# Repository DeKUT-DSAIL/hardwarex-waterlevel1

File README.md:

## hardwarex-waterlevel1
### A Low Cost LoRa Based River Water Level Data Acquisition System (Design Files)
#### Contents
- Arduino Nano based stage monitoring system - Kicad design files (etching pdf available)
- Multitech mDot based stage monitoring system - Kicad design files (etching pdf available)
- Arduino Nano based stage monitoring system - Arduino IDE code (Firmware)
- TTN (The Things Network) payload formatter for the Multitech mDot based stage monitoring system (in JavaScript)

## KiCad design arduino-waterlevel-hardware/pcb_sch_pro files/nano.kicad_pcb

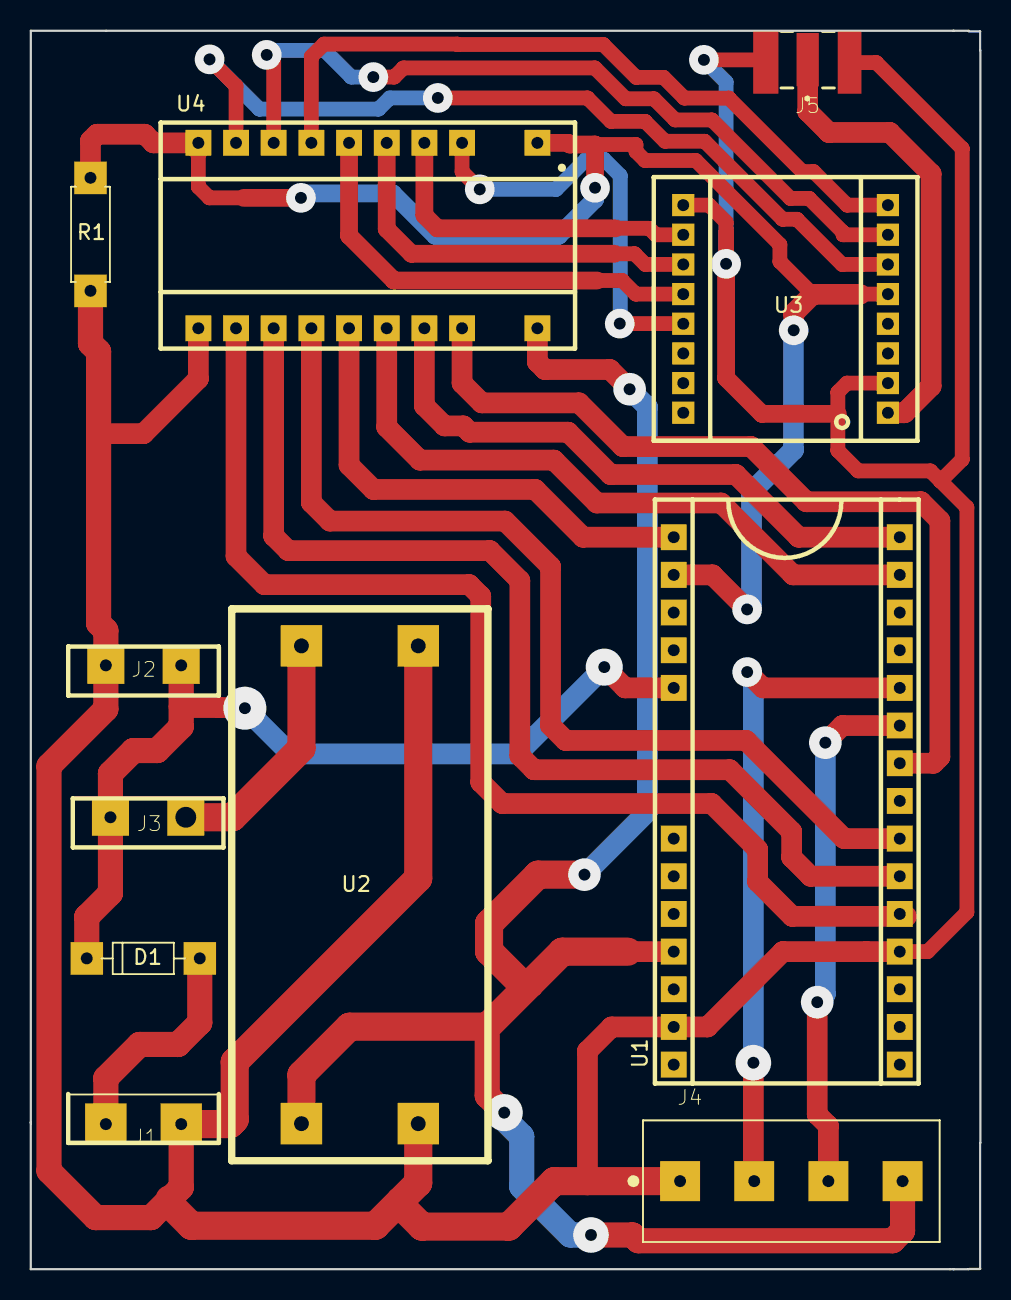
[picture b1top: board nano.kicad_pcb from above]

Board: 2 copper layers, 64.0 x 83.5 mm, 11 parts (0 on the bottom side), 23 nets.

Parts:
D1: D_DO-35_SOD27_P7.62mm_Horizontal
J1, J2, J3: TE_282815-2
J4: TE_282836-4
J5: SAMTEC_SMA-J-P-H-ST-EM1
R1: R_Axial_DIN0207_L6.3mm_D2.5mm_P7.62mm_Horizontal
U1: nano
U2: MT3608
U3: brake1
U4: SHIFT

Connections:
GND: J1.1, J2.1, J4.1, J5.2_1, J5.2_2, J5.3_1, J5.3_2, R1.1, U1.14, U1.19, U2.2, U2.4, U3.2, U3.9, U4.11
unnamed: D1.1, J2.2, J3.1
unnamed: D1.2, J1.2
unnamed: J3.2, U2.1
unnamed: J4.2, U1.26
unnamed: J4.3, U1.25
unnamed: J4.4, U1.12, U2.3, U4.20
unnamed: J5.1, U3.1
unnamed: R1.2, U1.2, U3.5, U4.1, U4.10
unnamed: U1.1, U4.15
unnamed: U1.20, U4.12
unnamed: U1.21, U4.13
unnamed: U1.22, U4.14
unnamed: U1.24, U4.18
unnamed: U1.29, U4.16
unnamed: U1.30, U4.17
unnamed: U3.6, U4.9
unnamed: U3.7, U4.8
unnamed: U3.8, U4.7
unnamed: U3.10, U4.4
unnamed: U3.11, U4.5
unnamed: U3.12, U4.6
unnamed: U3.13, U4.3

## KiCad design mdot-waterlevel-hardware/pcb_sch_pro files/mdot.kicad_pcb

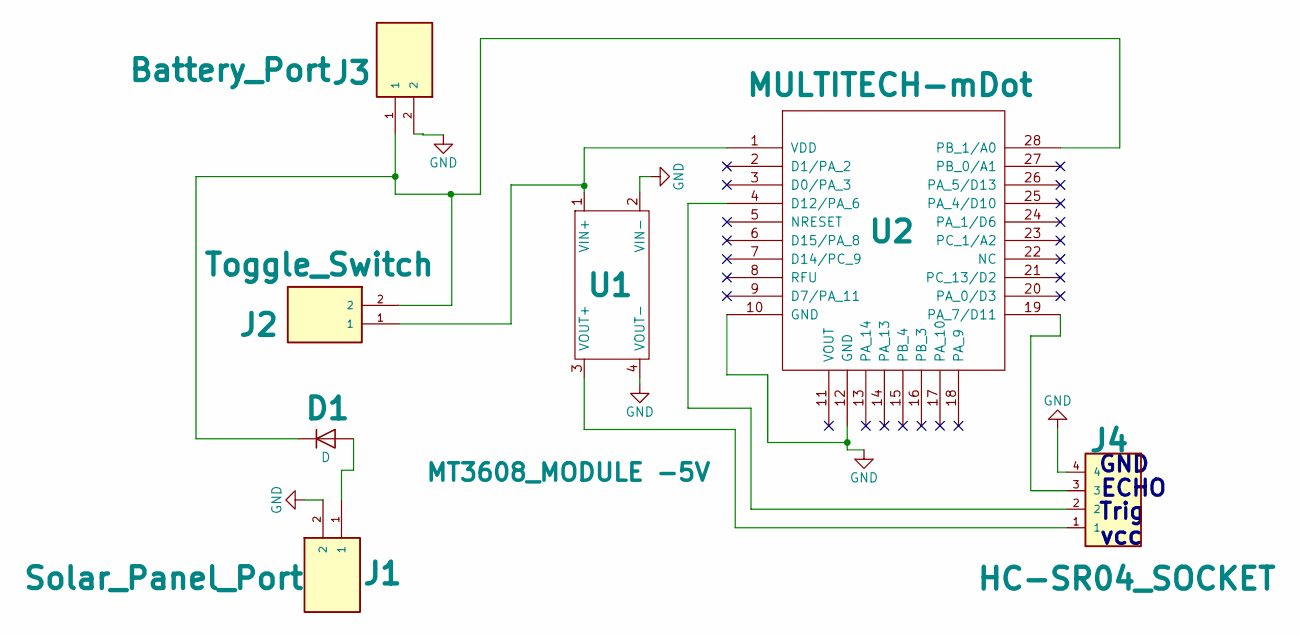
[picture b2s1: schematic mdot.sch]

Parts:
D1: D; D_5W_P12.70mm_Horizontal
J1: Solar_Panel_Port; TE_282815-2
J2: Toggle_Switch; TE_282815-2
J3: Battery_Port; TE_282815-2
J4: HC-SR04_SOCKET; TE_282836-4
U1: MT3608_MODULE -5V; MT3608
U2: MULTITECH-mDot; MDOT_TRIAL_BAT_CHARGER

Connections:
GND: J1.2, J3.2, J4.4, U1.2 (VIN-), U1.4 (VOUT-), U2.10 (GND), U2.12 (GND)
unnamed: D1.1 (K), J2.2, J3.1, U2.28 (PB_1/A0)
unnamed: D1.2 (A), J1.1
unnamed: J2.1, U1.1 (VIN+), U2.1 (VDD)
unnamed: J4.1, U1.3 (VOUT+)
unnamed: J4.2, U2.4 (D12/PA_6)
unnamed: J4.3, U2.19 (PA_7/D11)

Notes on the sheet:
vcc
Trig
ECHO
GND

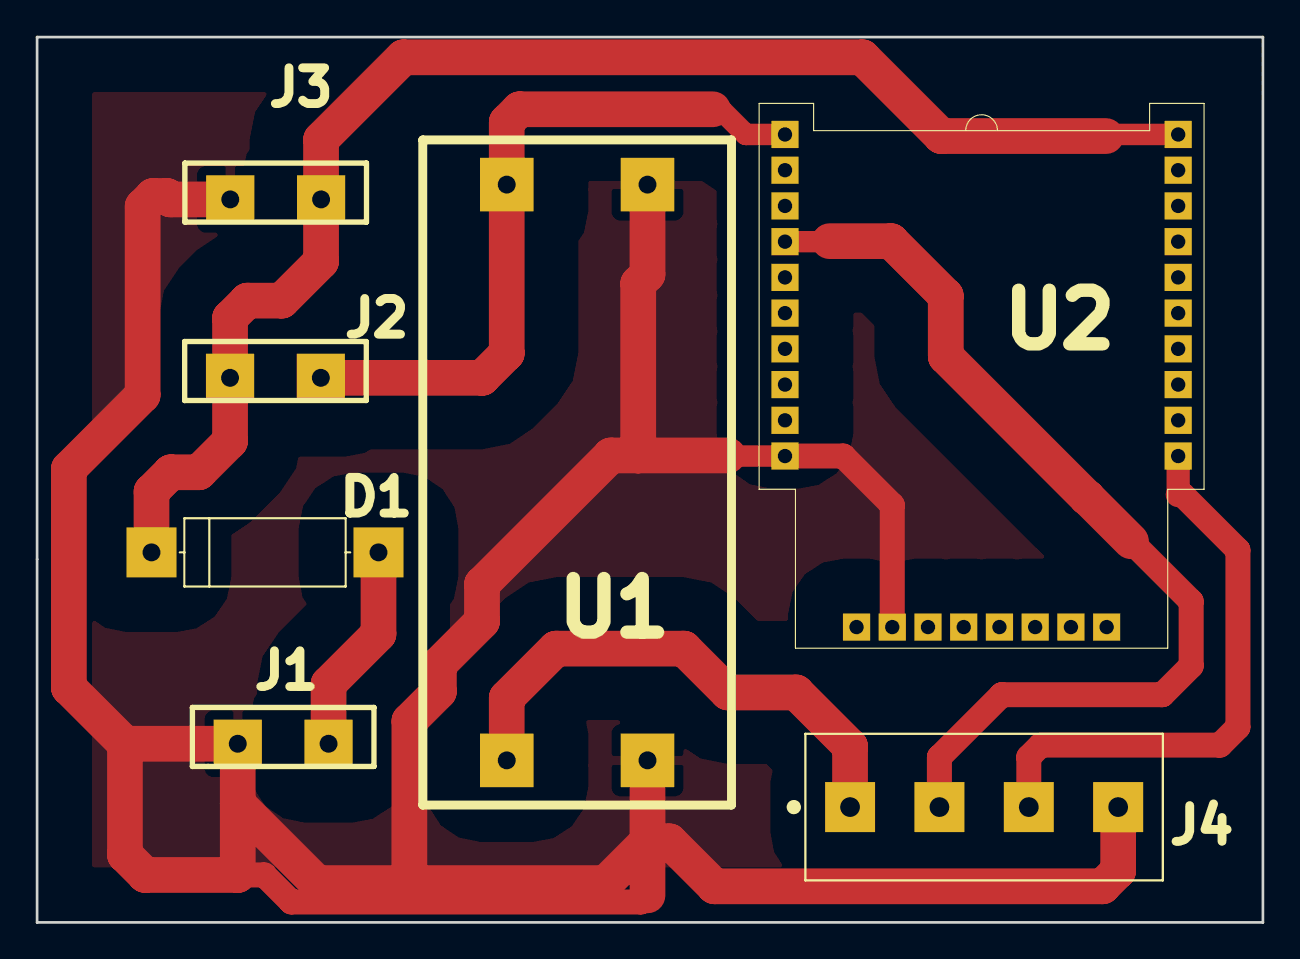
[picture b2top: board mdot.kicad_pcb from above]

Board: 2 copper layers, 68.6 x 49.5 mm, 7 parts (0 on the bottom side), 7 nets.

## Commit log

2022-03-23 hardware and software files
